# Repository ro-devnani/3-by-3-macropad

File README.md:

# 3-by-3-macropad
For the Emerald Makerspace Club, this is a small 9 switch + 1 rotary encoder macropad meant help students learn the basics of PCB design and mechanical keyboards.

## Components/Parts
- 1 RP2040 Pro Micro
- 9 Kalih hotswap sockets
- 9 MX switches
- 9 Cherry Keycaps
- 10 tht DO-35 diodes
- 1 Rotary Encoder
  These components were chosen to minimize cost, keep the macropad relatively basic, and to make it easy to solder.

## Firmware
The firmware is made with QMK.

## Pictures
### PCB

### CAD

### Final Product
to come soon

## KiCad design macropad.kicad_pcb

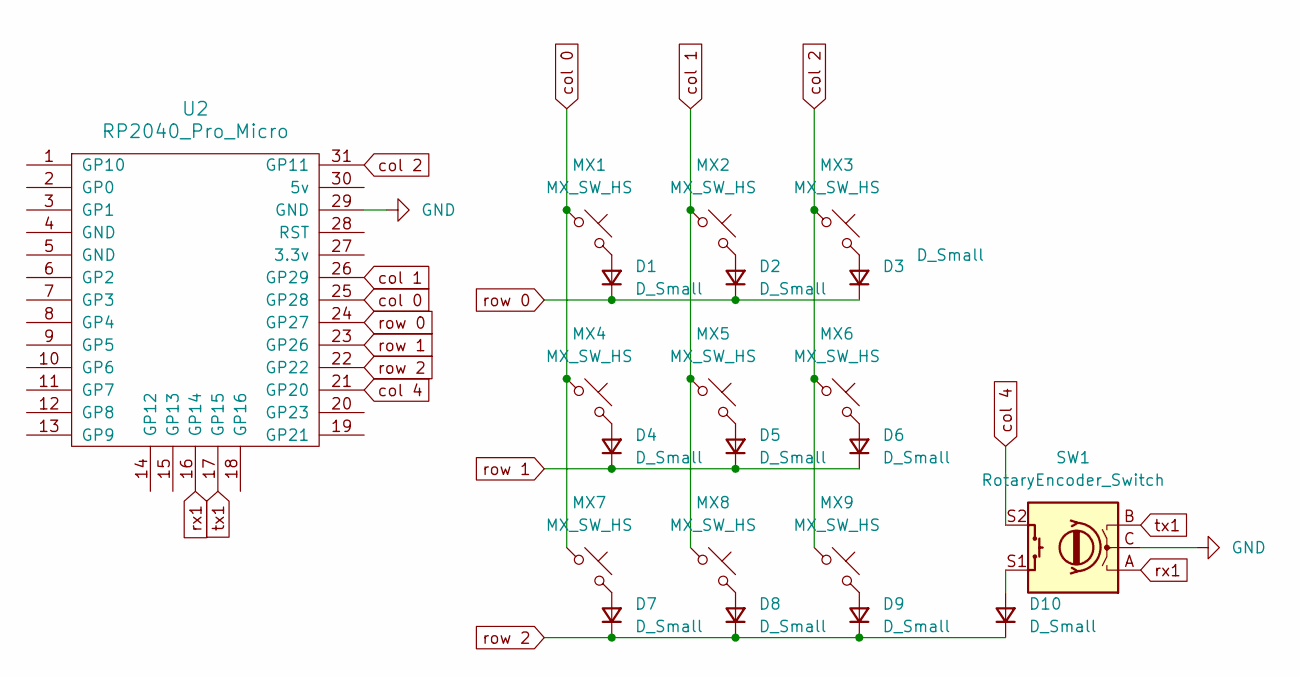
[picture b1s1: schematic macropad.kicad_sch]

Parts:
D1, D2, D3, D4, D5, D6, D7, D8, D9, D10: D_Small; Diode_DO-35
MX1, MX2, MX3, MX4, MX5, MX6, MX7, MX8, MX9: MX_SW_HS; Hotswap_MX_1.00u
SW1: RotaryEncoder_Switch; RotaryEncoder_Alps_EC11E-Switch_Vertical_H20mm
U2: RP2040_Pro_Micro

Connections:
GND: SW1.C, U2.29 (GND)
unnamed: D1.2 (A), MX1.2
unnamed: D2.2 (A), MX2.2
unnamed: D3.2 (A), MX3.2
unnamed: D4.2 (A), MX4.2
unnamed: D5.2 (A), MX5.2
unnamed: D6.2 (A), MX6.2
unnamed: D7.2 (A), MX7.2
unnamed: D8.2 (A), MX8.2
unnamed: D9.2 (A), MX9.2
unnamed: D10.2 (A), SW1.S1
col 0: MX1.1, MX4.1, MX7.1, U2.25 (GP28)
col 1: MX2.1, MX5.1, MX8.1, U2.26 (GP29)
col 2: MX3.1, MX6.1, MX9.1, U2.31 (GP11)
col 4: SW1.S2, U2.21 (GP20)
row 0: D1.1 (K), D2.1 (K), D3.1 (K), U2.24 (GP27)
row 1: D4.1 (K), D5.1 (K), D6.1 (K), U2.23 (GP26)
row 2: D7.1 (K), D8.1 (K), D9.1 (K), D10.1 (K), U2.22 (GP22)
rx1: SW1.A, U2.16 (GP14)
tx1: SW1.B, U2.17 (GP15)

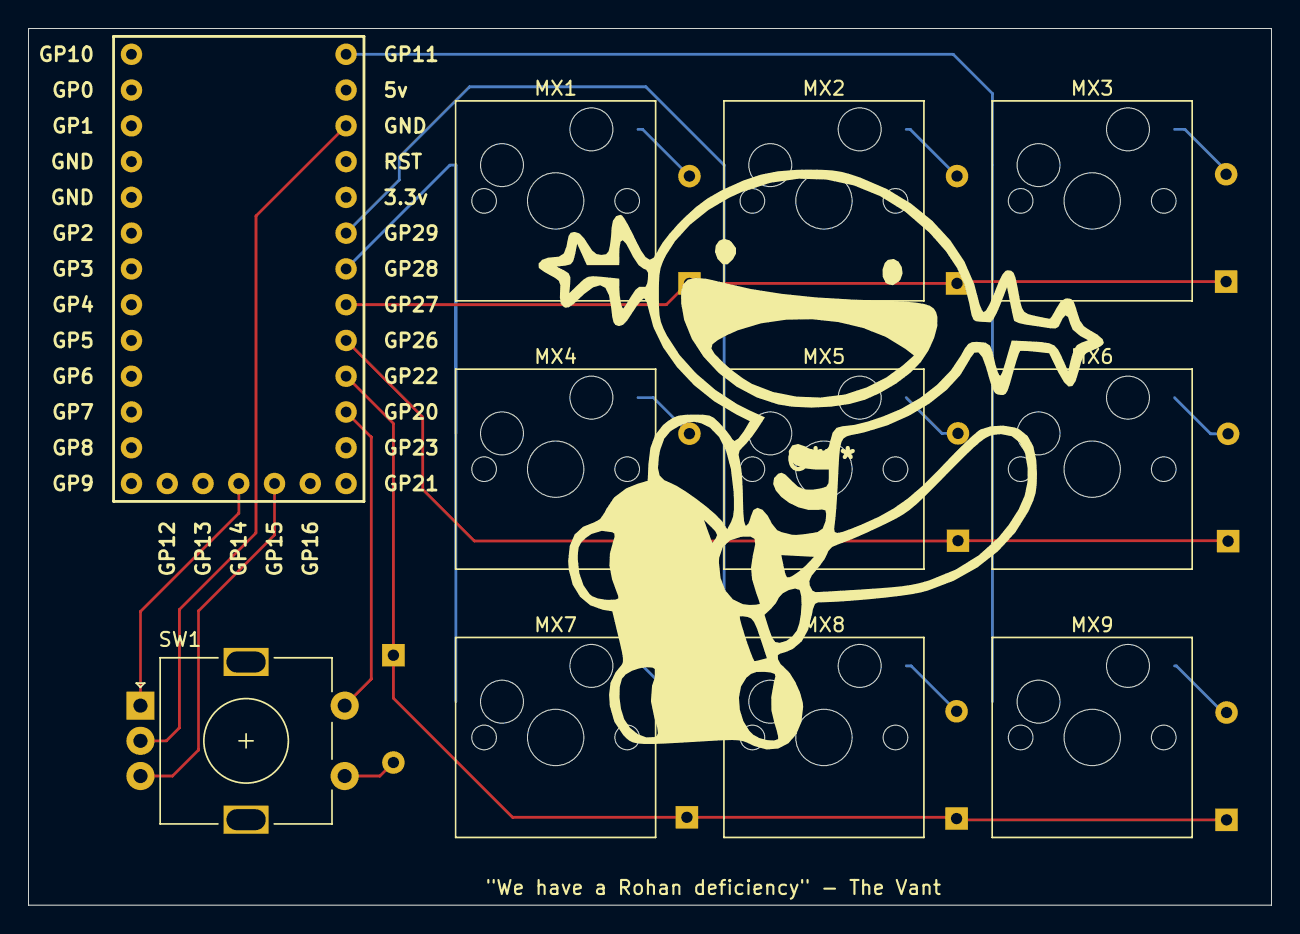
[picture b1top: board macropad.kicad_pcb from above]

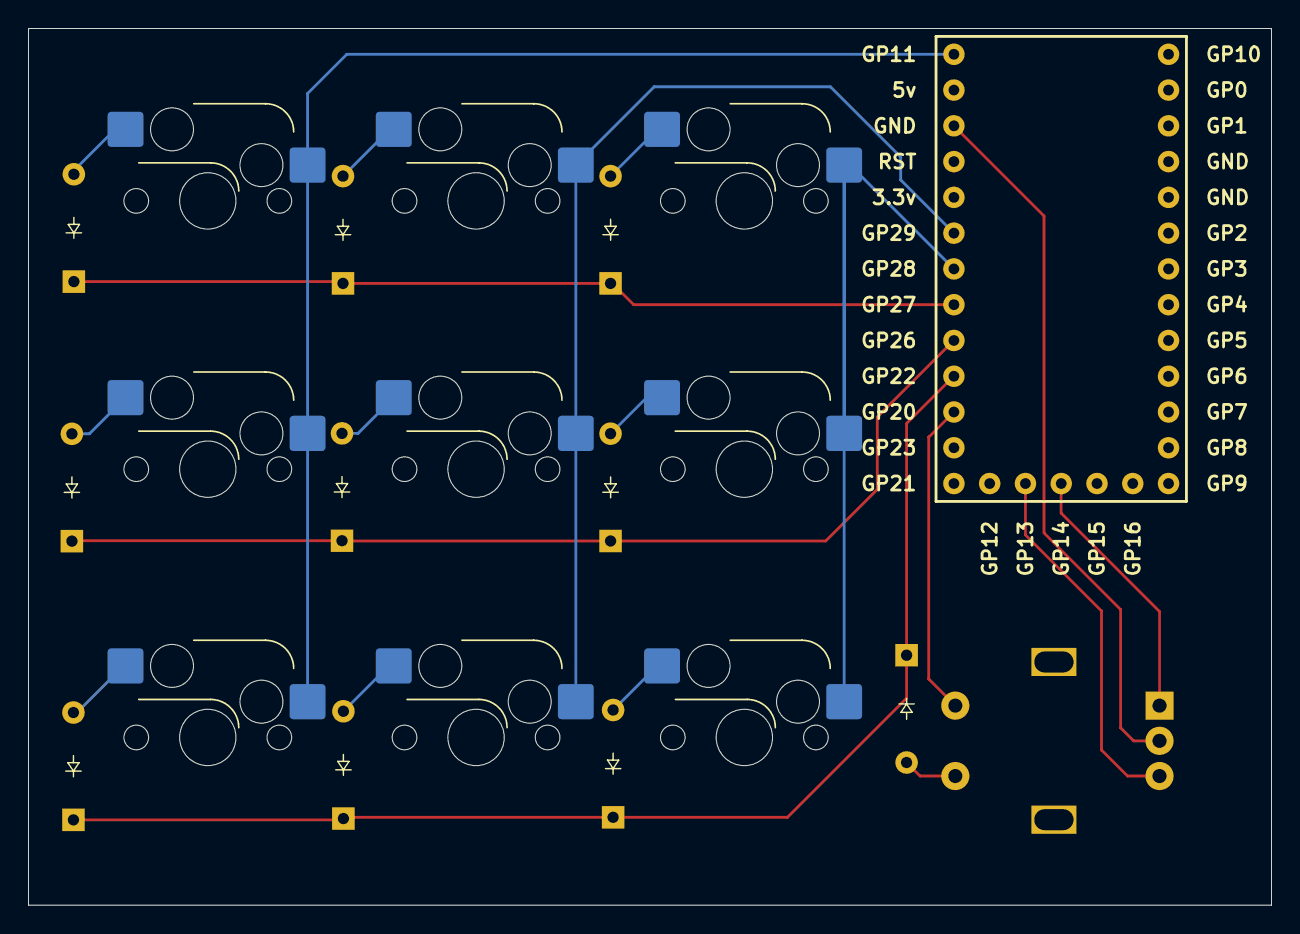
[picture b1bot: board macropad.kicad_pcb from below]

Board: 2 copper layers, 88.3 x 62.3 mm, 21 parts (10 on the bottom side), 20 nets.

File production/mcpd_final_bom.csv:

Designator,Footprint,Quantity,Value,LCSC Part #
"D1, D10, D2, D3, D4, D5, D6, D7, D8, D9",Diode_DO-35,10,D_Small,
"MX1, MX2, MX3, MX4, MX5, MX6, MX7, MX8, MX9",Hotswap_MX_1.00u,9,MX_SW_HS,
SW1,RotaryEncoder_Alps_EC11E-Switch_Vertical_H20mm,1,RotaryEncoder_Switch,
U2,RP2040_Pro_Micro,1,RP2040_Pro_Micro,

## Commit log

2025-11-03 Create models
2025-11-03 Create CAD
2025-11-08 Fix bom.csv
2025-11-08 Create firmware folder
2025-11-08 Add firmware files
2025-11-12 Rename geber.zip to gerber.zip
2025-11-18 clean repo
